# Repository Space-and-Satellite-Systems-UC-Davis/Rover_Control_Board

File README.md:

# Rover Control Board
Embedded systems board for interfacing with sensors, motor controllers, and other boards on the Rover. 
## Rover Control Board v1

## Rover Controls Sensor Breakout Board

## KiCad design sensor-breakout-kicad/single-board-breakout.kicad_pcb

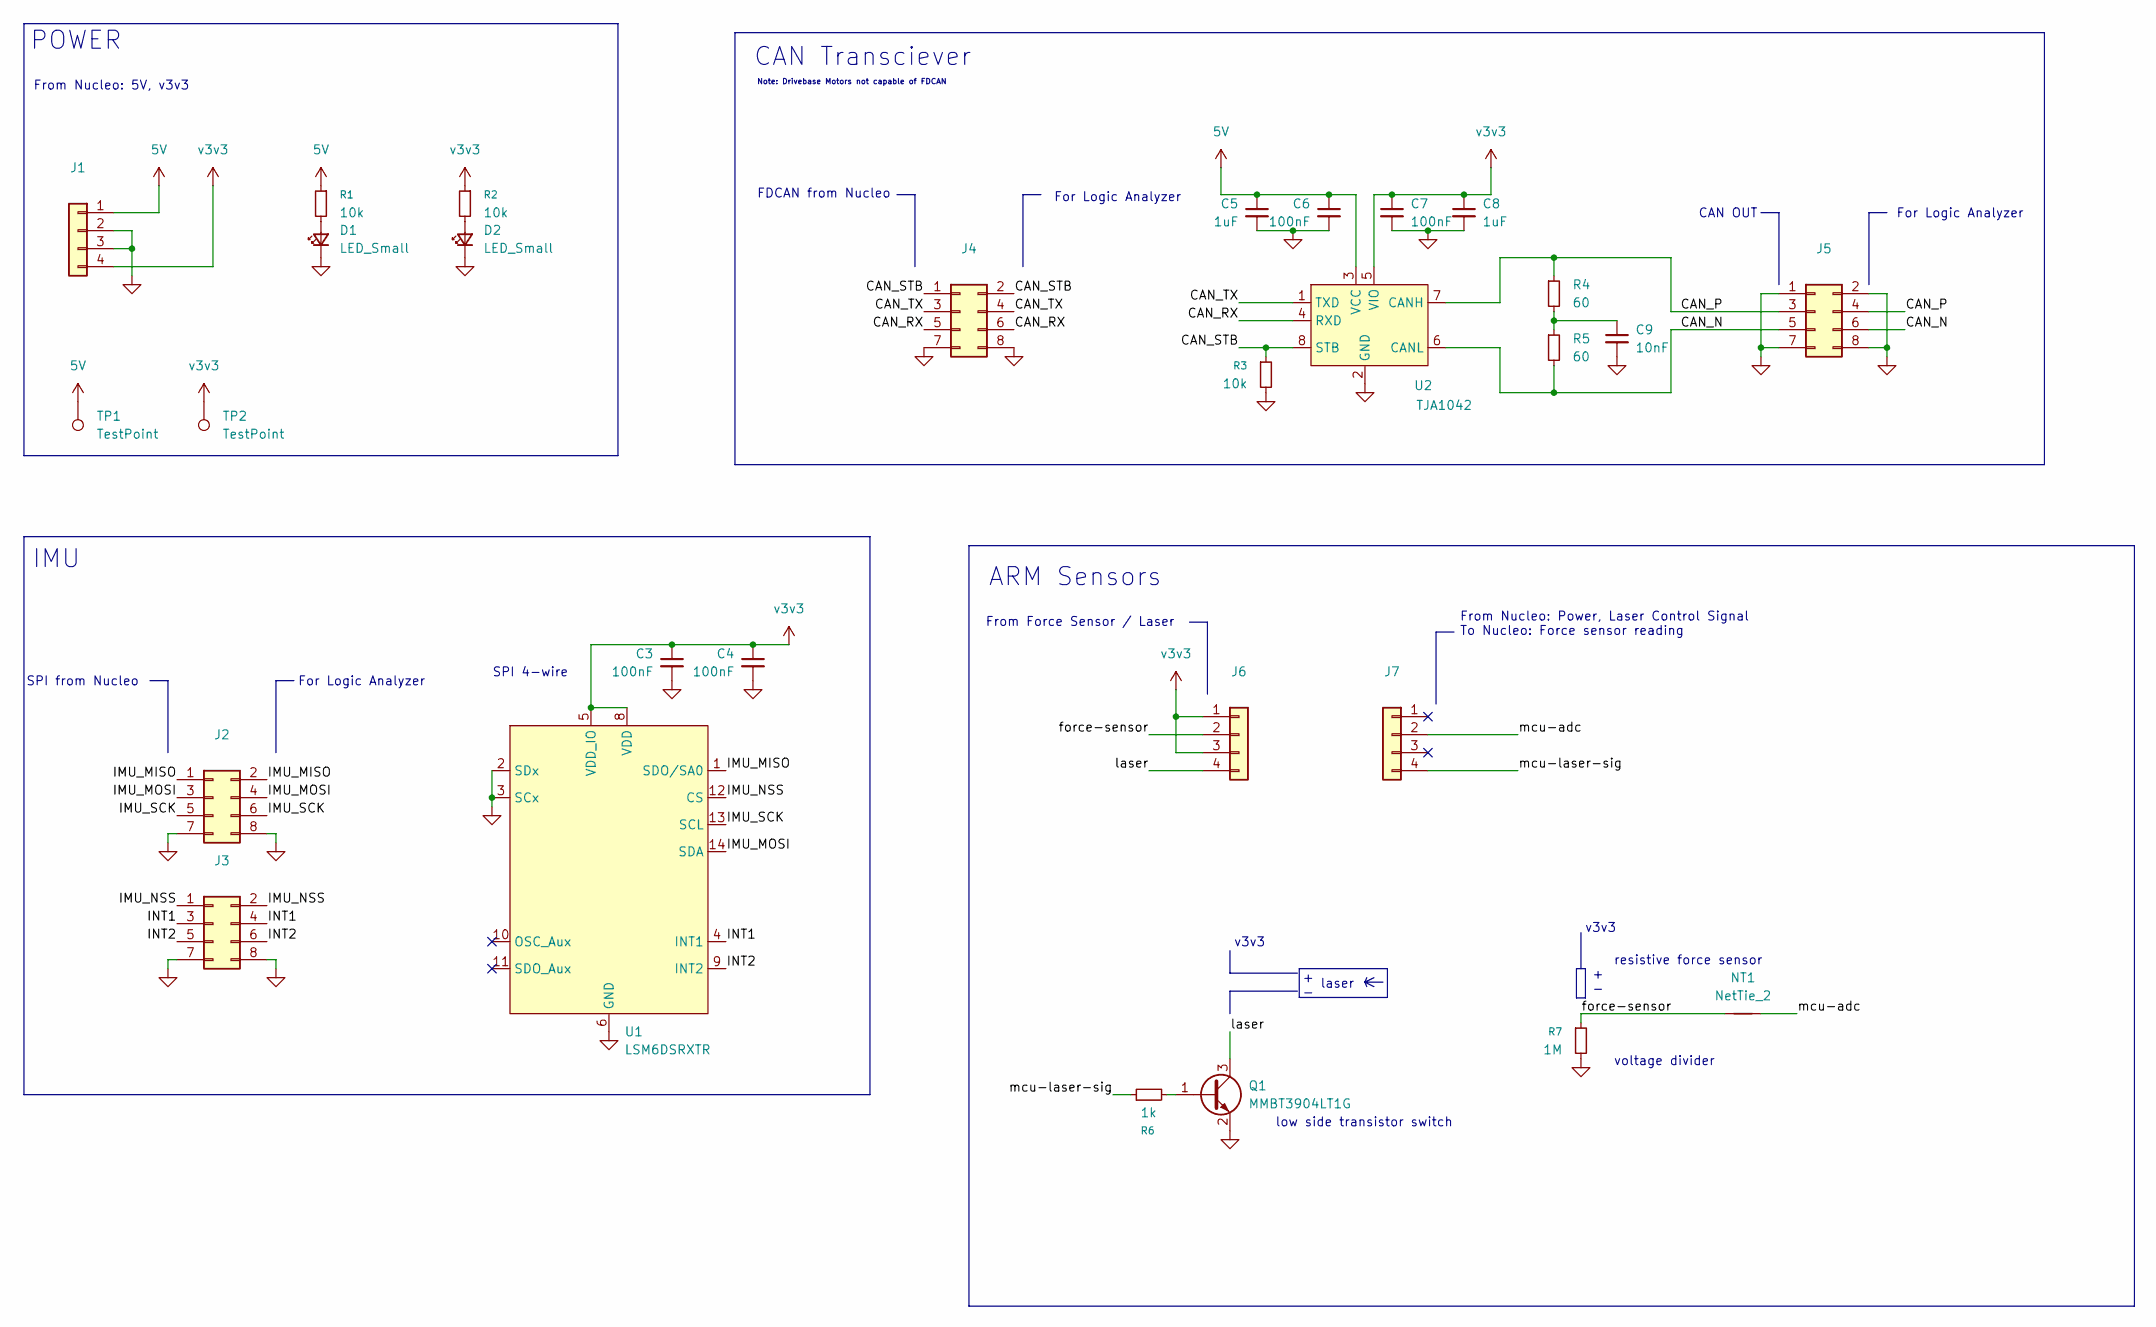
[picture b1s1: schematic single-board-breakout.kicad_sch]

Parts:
C3, C4, C6, C7: 100nF; C_0402_1005Metric; LCSC Part # C100072
C5, C8: 1uF; C_0402_1005Metric; LCSC Part # C52923
C9: 10nF; C_0402_1005Metric; LCSC Part # C15195
D1, D2: LED_Small; LED_0603_1608Metric
J1, J6, J7: Conn_01x04; PinHeader_1x04_P2.54mm_Vertical
J2, J3, J4, J5: Conn_02x04_Odd_Even; PinHeader_2x04_P2.54mm_Vertical
NT1: NetTie_2; NetTie_0.2mm
Q1: MMBT3904LT1G; SOT-23
R1, R2, R3: 10k; R_0402_1005Metric; LCSC Part # C71617
R4, R5: 60; R_0402_1005Metric; LCSC Part # C416565
R6: 1k; R_0402_1005Metric; LCSC Part # C71617
R7: 1M; R_0402_1005Metric; LCSC Part # C71617
TP1, TP2: TestPoint; TestPoint_Pad_D2.0mm
U1: LSM6DSRXTR; LCSC Part # C5267399
U2: TJA1042; SOIC-8_3.9x4.9mm_P1.27mm; LCSC Part # C53670

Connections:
5V: C5.1, C6.1, J1.1, R1.1, TP1.1 (1_1), U2.3 (VCC)
/CAN_N: J5.5, J5.6, R5.2, U2.6 (CANL)
/CAN_P: J5.3, J5.4, R4.1, U2.7 (CANH)
/CAN_RX: J4.5, J4.6, U2.4 (RXD)
/CAN_STB: J4.1, J4.2, R3.1, U2.8 (STB)
/CAN_TX: J4.3, J4.4, U2.1 (TXD)
/IMU_MISO: J2.1, J2.2, U1.1 (SDO/SA0)
/IMU_MOSI: J2.3, J2.4, U1.14 (SDA)
/IMU_NSS: J3.1, J3.2, U1.12 (CS)
/IMU_SCK: J2.5, J2.6, U1.13 (SCL)
/INT1: J3.3, J3.4, U1.4 (INT1)
/INT2: J3.5, J3.6, U1.9 (INT2)
/force-sensor: J6.2, NT1.1, R7.1
/laser: J6.4, Q1.3 (C)
/mcu-adc: J7.2, NT1.2
/mcu-laser-sig: J7.4, R6.1
GND: C3.2, C4.2, C5.2, C6.2, C7.2, C8.2, C9.2, D1.1 (K), D2.1 (K), J1.2, J1.3, J2.7, J2.8, J3.7, J3.8, J4.7, J4.8, J5.1, J5.2, J5.7, J5.8, Q1.2 (E), R3.2, R7.2, U1.2 (SDx), U1.3 (SCx), U1.6 (GND), U1.7 (GND), U2.2 (GND)
unnamed: C9.1, R4.2, R5.1
unnamed: D1.2 (A), R1.2
unnamed: D2.2 (A), R2.2
unnamed: Q1.1 (B), R6.2
v3v3: C3.1, C4.1, C7.1, C8.1, J1.4, J6.1, J6.3, R2.1, TP2.1 (1_1), U1.5 (VDD_IO), U1.8 (VDD), U2.5 (VIO)

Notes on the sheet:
To Nucleo: Force sensor reading
CAN OUT
From Force Sensor / Laser
SPI from Nucleo
For Logic Analyzer
v3v3
resistive force sensor
IMU
CAN Transciever
From Nucleo: Power, Laser Control Signal
+ -
Note: Drivebase Motors not capable of FDCAN
SPI 4-wire
From Nucleo: 5V, v3v3
voltage divider
POWER
laser
low side transistor switch
ARM Sensors
FDCAN from Nucleo

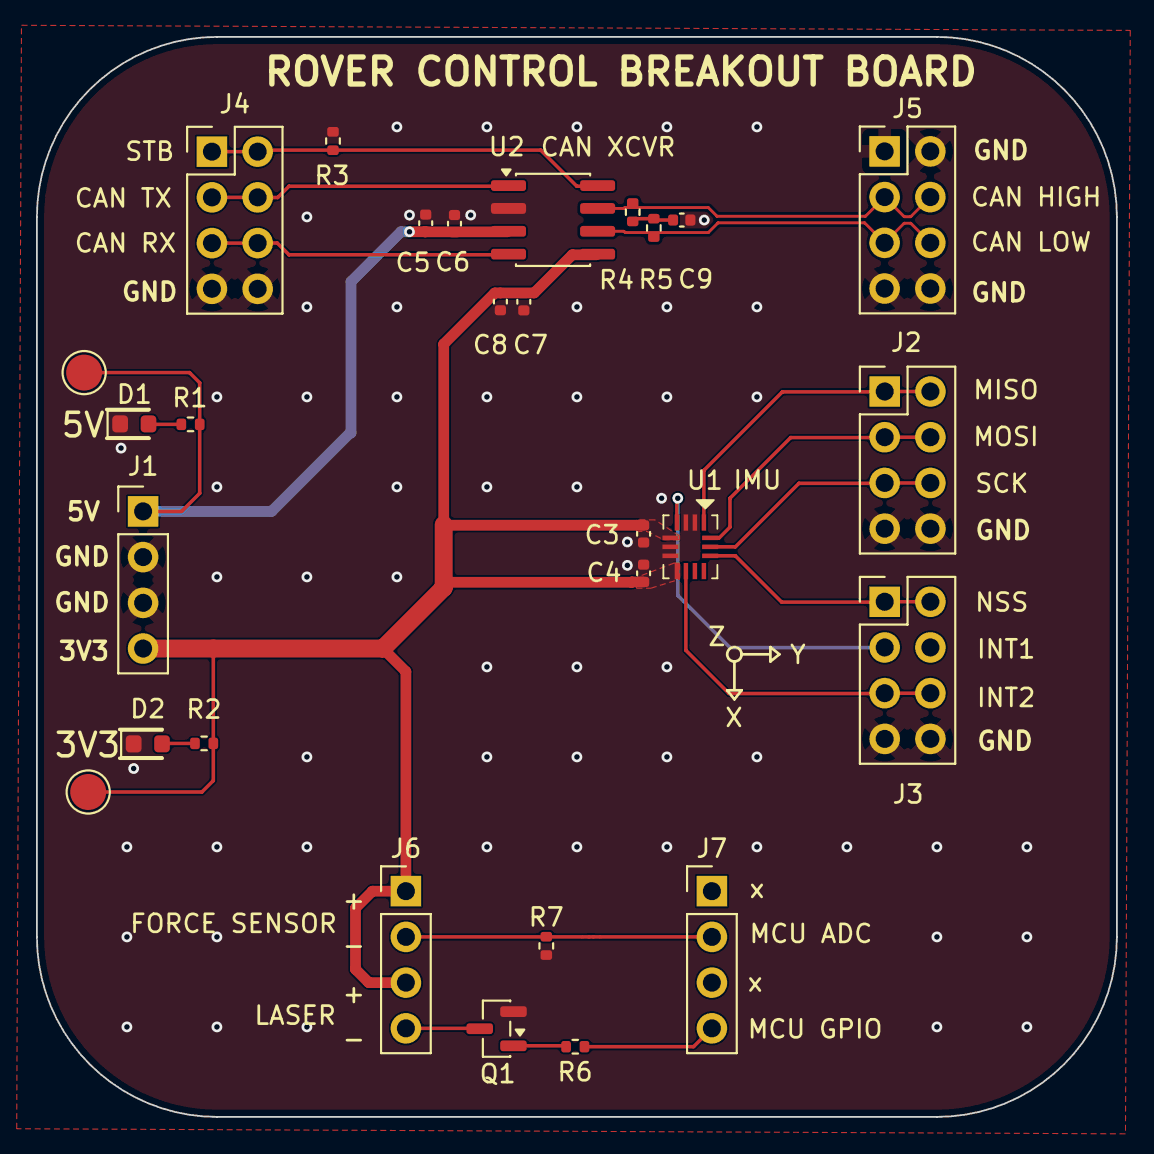
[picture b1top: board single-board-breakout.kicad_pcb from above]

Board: 2 copper layers, 60.0 x 60.0 mm, 29 parts (0 on the bottom side), 22 nets.

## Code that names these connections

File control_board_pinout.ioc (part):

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Mcu.Name=STM32G474V(B-C-E)Tx
Mcu.Package=LQFP100
Mcu.UserName=STM32G474VBTx
PA0.Signal=S_TIM2_CH1
PA1.Signal=S_TIM5_CH2
PA10.Mode=Asynchronous
PA10.Signal=USART1_RX
PA11.Mode=Device
PA11.Signal=USB_DM
PA12.Mode=Device
PA12.Signal=USB_DP
PA13.Mode=Serial_Wire
PA13.Signal=SYS_JTMS-SWDIO
PA14.Mode=Serial_Wire
PA14.Signal=SYS_JTCK-SWCLK
PA15.Signal=S_TIM8_CH1
PA2.Signal=S_TIM2_CH3
PA3.Signal=S_TIM2_CH4
PA4.GPIOParameters=GPIO_Label
PA4.GPIO_Label=DIR6
PA4.Signal=GPIO_Output
PA5.Mode=Full_Duplex_Master
PA5.Signal=SPI1_SCK
PA6.Mode=Full_Duplex_Master
PA6.Signal=SPI1_MISO
PA7.Mode=Full_Duplex_Master
PA7.Signal=SPI1_MOSI
PA9.Mode=Asynchronous
PA9.Signal=USART1_TX
PB0.GPIOParameters=GPIO_Label
PB0.GPIO_Label=INT1
PB0.Signal=GPIO_Output
PB10.GPIOParameters=GPIO_Label
PB10.GPIO_Label=LED4
PB10.Signal=GPIO_Output
PB11.GPIOParameters=GPIO_Label
PB11.GPIO_Label=LED6
PB11.Signal=GPIO_Output
PB12.GPIOParameters=GPIO_Label
PB12.GPIO_Label=LED1
PB12.Signal=GPIO_Output
PB13.Mode=Full_Duplex_Master
PB13.Signal=SPI2_SCK
PB14.Mode=Full_Duplex_Master
PB14.Signal=SPI2_MISO
PB15.Mode=Full_Duplex_Master
PB15.Signal=SPI2_MOSI
PB3.GPIOParameters=GPIO_Label
PB3.GPIO_Label=DIR1
PB3.Signal=GPIO_Output
PB4.Signal=S_TIM3_CH1
PB5.Signal=S_TIM3_CH2
PB6.Signal=S_TIM4_CH1
PB7.Signal=S_TIM4_CH2
PB9.GPIOParameters=GPIO_Label
PB9.GPIO_Label=DIR2
PB9.Signal=GPIO_Output
PC0.Signal=S_TIM1_CH1
PC1.Signal=S_TIM1_CH2
PC10.Mode=Asynchronous
PC10.Signal=USART3_TX
PC11.Mode=Asynchronous
PC11.Signal=USART3_RX
PC2.Signal=S_TIM1_CH3
PC3.GPIOParameters=GPIO_Label
PC3.GPIO_Label=DIR4
PC3.Signal=GPIO_Output
PC4.GPIOParameters=GPIO_Label
PC4.GPIO_Label=NSS
PC4.Signal=GPIO_Output
PC5.GPIOParameters=GPIO_Label
PC5.GPIO_Label=INT2
PC5.Signal=GPIO_Output
PC6.Mode=I2C
PC6.Signal=I2C4_SCL
PC7.Mode=I2C
PC7.Signal=I2C4_SDA
PC8.Mode=I2C
PC8.Signal=I2C3_SCL
PC9.Mode=I2C
PC9.Signal=I2C3_SDA
PD0.Mode=FDCAN_Activate
PD0.Signal=FDCAN1_RX
PD1.Mode=FDCAN_Activate
PD1.Signal=FDCAN1_TX
PD10.GPIOParameters=GPIO_Label
PD10.GPIO_Label=U_SW2
PD10.Signal=GPIO_Output
PD11.GPIOParameters=GPIO_Label
PD11.GPIO_Label=U_SW1
PD11.Signal=GPIO_Output
PD12.GPIOParameters=GPIO_Label
PD12.GPIO_Label=TRI_G
PD12.Signal=GPIO_Output
PD13.GPIOParameters=GPIO_Label
PD13.GPIO_Label=TRI_R
PD13.Signal=GPIO_Output
PD14.GPIOParameters=GPIO_Label
PD14.GPIO_Label=TRI_B
PD14.Signal=GPIO_Output
PD2.Signal=GPIO_Output
PD3.Signal=GPIO_Output
PD4.Signal=GPIO_Output
PD5.Mode=Asynchronous
PD5.Signal=USART2_TX
PD6.Mode=Asynchronous
PD6.Signal=USART2_RX
PD8.GPIOParameters=GPIO_Label
PD8.GPIO_Label=NSS2
PD8.Signal=GPIO_Output
PE0.Signal=S_TIM16_CH1
PE1.Signal=S_TIM20_CH4
PE10.Mode=IN14-Single-Ended
PE10.Signal=ADC3_IN14
PE11.GPIOParameters=GPIO_Label
PE11.GPIO_Label=LASER
PE11.Signal=GPIO_Output
PE12.GPIOParameters=GPIO_Label
PE12.GPIO_Label=L_SW1
PE12.Signal=GPIO_Output
PE13.GPIOParameters=GPIO_Label
PE13.GPIO_Label=L_SW2
PE13.Signal=GPIO_Output
PE14.GPIOParameters=GPIO_Label
PE14.GPIO_Label=L_SW3
PE14.Signal=GPIO_Output
PE15.GPIOParameters=GPIO_Label
PE15.GPIO_Label=LED5
PE15.Signal=GPIO_Output
PE2.Signal=S_TIM20_CH1
PE3.Signal=S_TIM20_CH2
PE4.Signal=S_TIM3_CH3
PE5.GPIOParameters=GPIO_Label
PE5.GPIO_Label=DIR3
PE5.Signal=GPIO_Output
PE8.GPIOParameters=GPIO_Label
PE8.GPIO_Label=LED2
PE8.Signal=GPIO_Output
PE9.GPIOParameters=GPIO_Label
PE9.GPIO_Label=LED3
PE9.Signal=GPIO_Output
PF0-OSC_IN.Mode=HSE-External-Oscillator
PF0-OSC_IN.Signal=RCC_OSC_IN
PF1-OSC_OUT.Mode=HSE-External-Oscillator
PF1-OSC_OUT.Signal=RCC_OSC_OUT
PF2.GPIOParameters=GPIO_Label
PF2.GPIO_Label=DIR5
PF2.Signal=GPIO_Output
RCC.HSE_VALUE=16000000
RCC.SYSCLKFreq_VALUE=144000000
RCC.SYSCLKSource=RCC_SYSCLKSOURCE_PLLCLK
board=custom
